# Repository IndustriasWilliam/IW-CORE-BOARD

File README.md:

"# IW-CORE-BOARD" 
cmd.exe /C copy/Y "${BuildArtifactFileBaseName}.elf" "..\QSPI_FlashLoader.stldr"

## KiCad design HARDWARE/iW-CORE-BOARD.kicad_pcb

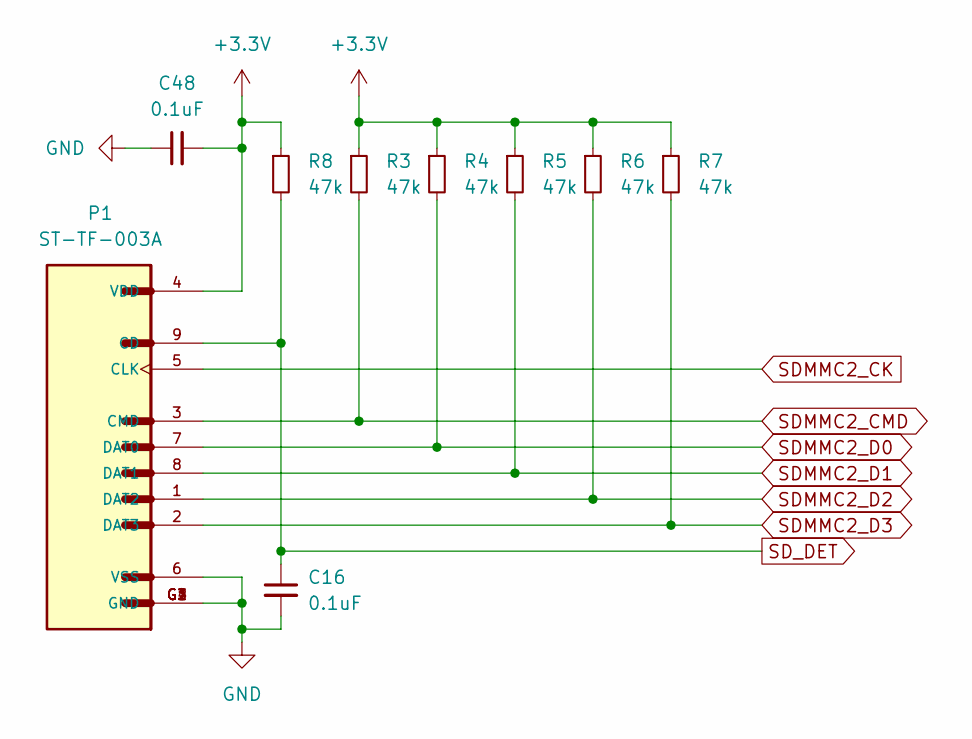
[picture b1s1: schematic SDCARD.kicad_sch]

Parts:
C16, C48: 0.1uF; C_0603_1608Metric
P1: ST-TF-003A; SUNTECH_ST-TF-003A
R3, R4, R5, R6, R7, R8: 47k; R_0603_1608Metric

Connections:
+3.3V: C48.2, P1.4 (VDD), R3.1, R4.1, R5.1, R6.1, R7.1, R8.1; also elsewhere on the board
GND: C16.2, C48.1, P1.6 (VSS), P1.G1 (GND), P1.G2 (GND), P1.G3 (GND), P1.G4 (GND); also elsewhere on the board
SDMMC2_CK: P1.5 (CLK); also elsewhere on the board
SDMMC2_CMD: P1.3 (CMD), R3.2; also elsewhere on the board
SDMMC2_D0: P1.7 (DAT0), R4.2; also elsewhere on the board
SDMMC2_D1: P1.8 (DAT1), R5.2; also elsewhere on the board
SDMMC2_D2: P1.1 (DAT2), R6.2; also elsewhere on the board
SDMMC2_D3: P1.2 (DAT3), R7.2; also elsewhere on the board
SD_DET: C16.1, P1.9 (CD), R8.2; also elsewhere on the board

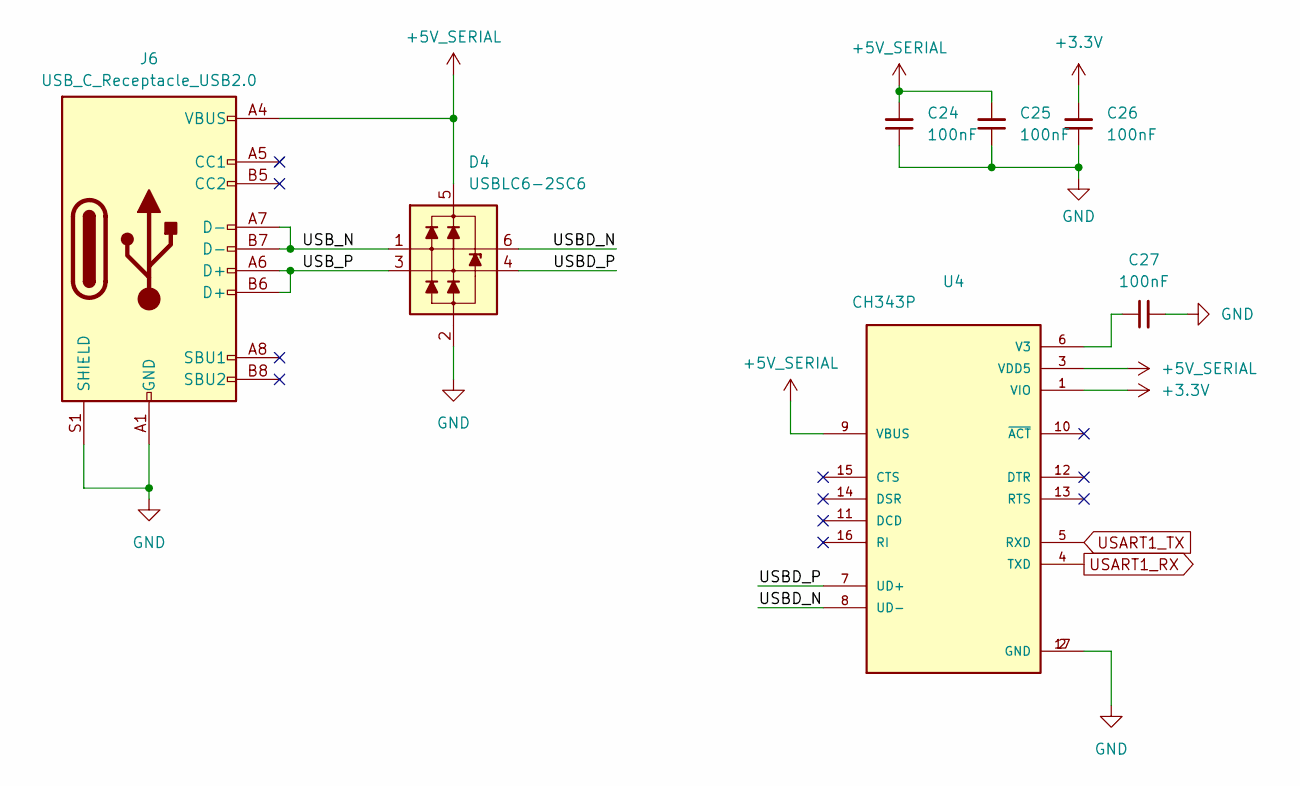
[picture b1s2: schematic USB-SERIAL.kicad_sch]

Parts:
C24, C25, C26, C27: 100nF; C_0603_1608Metric
D4: USBLC6-2SC6; SOT-23-6
J6: USB_C_Receptacle_USB2.0; USB_C_Receptacle_G-Switch_GT-USB-7010ASV
U4: CH343P; QFN50P300X300X80-17N; PARTREV 1E

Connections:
+3.3V: C26.2, U4.1 (VIO); also elsewhere on the board
+5V_SERIAL: C24.2, C25.2, D4.5 (VP), J6.A4 (VBUS), J6.A9 (VBUS), J6.B4 (VBUS), J6.B9 (VBUS), U4.3 (VDD5), U4.9 (VBUS); also elsewhere on the board
/USB-SERIAL/USBD_N: D4.6 (L1), U4.8 (UD-)
/USB-SERIAL/USBD_P: D4.4 (L2), U4.7 (UD+)
/USB-SERIAL/USB_N: D4.1 (L1), J6.A7 (D-), J6.B7 (D-)
/USB-SERIAL/USB_P: D4.3 (L2), J6.A6 (D+), J6.B6 (D+)
GND: C24.1, C25.1, C26.1, C27.2, D4.2 (VN), J6.A1 (GND), J6.A12 (GND), J6.B1 (GND), J6.B12 (GND), J6.S1 (SHIELD), U4.2 (GND), U4.17 (GND); also elsewhere on the board
unnamed: C27.1, U4.6 (V3)
USART1_RX: U4.4 (TXD); also elsewhere on the board
USART1_TX: U4.5 (RXD); also elsewhere on the board

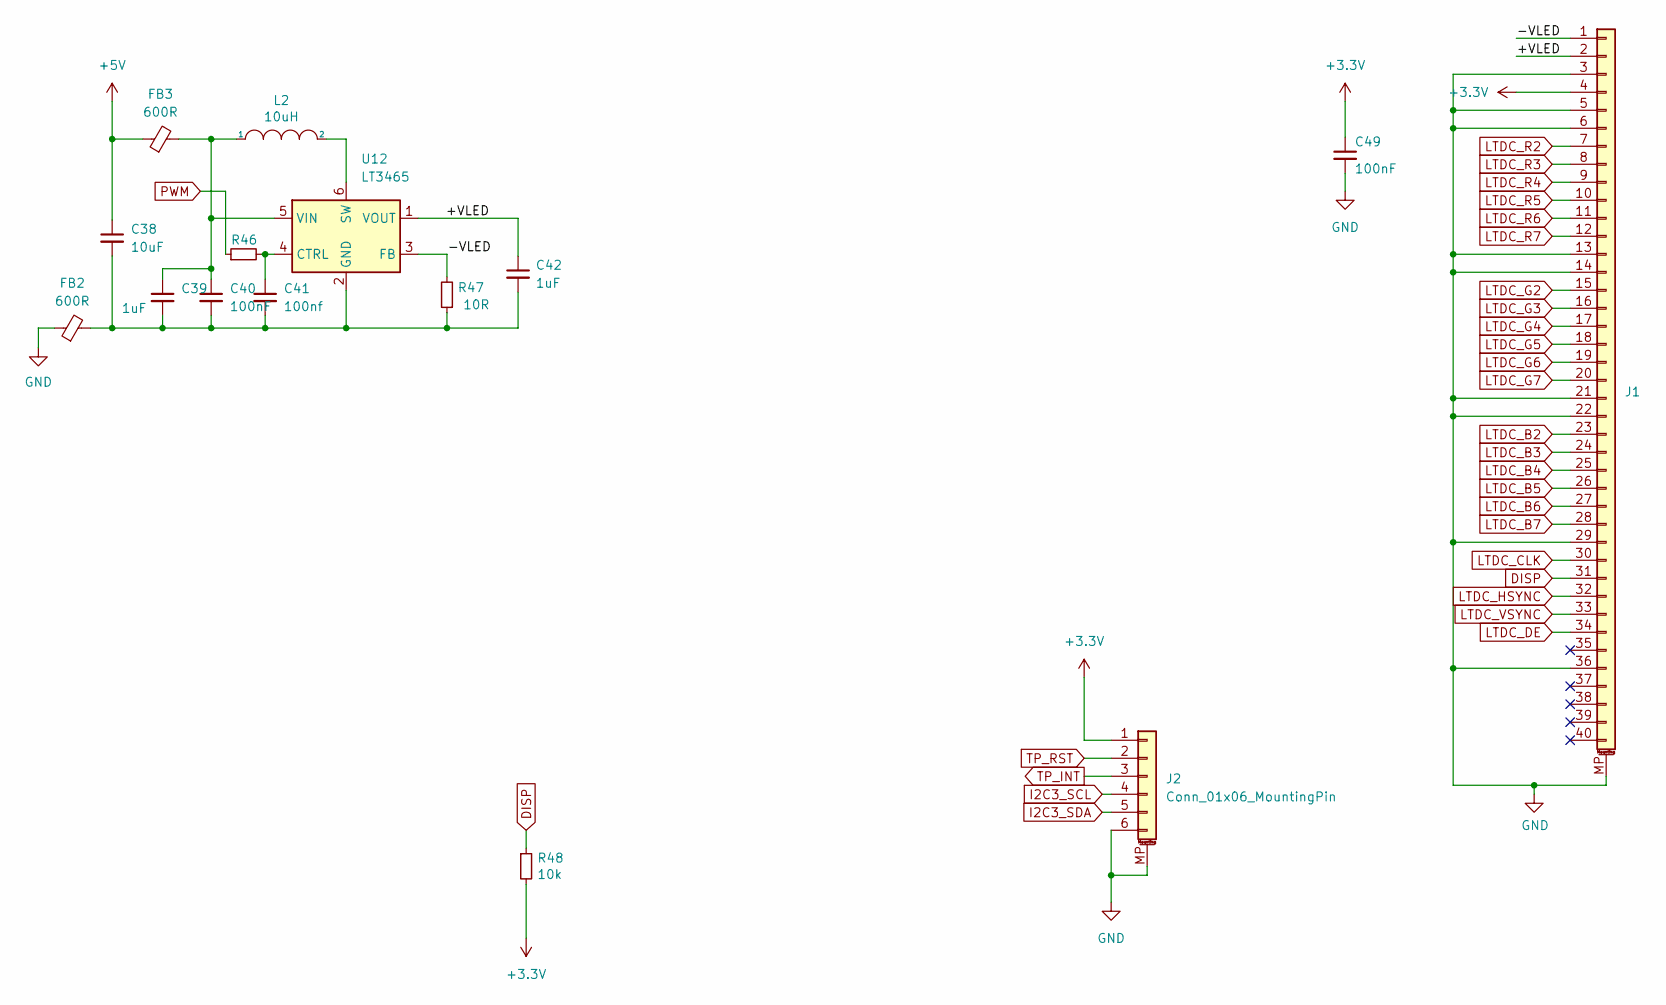
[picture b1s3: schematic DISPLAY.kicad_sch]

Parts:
C38: 10uF; C_0805_2012Metric
C39, C42: 1uF; C_0603_1608Metric
C40, C49: 100nF; C_0603_1608Metric
C41: 100nf; C_0603_1608Metric
FB2, FB3: 600R; L_0603_1608Metric
J1: Conn_01x40_MountingPin; TE_4-1734839-0_1x40-1MP_P0.5mm_Horizontal
J2: Conn_01x06_MountingPin; TE_0-1734839-6_1x06-1MP_P0.5mm_Horizontal
L2: 10uH; L_0805_2012Metric
R46: 5k; R_0603_1608Metric
R47: 10R; R_0603_1608Metric
R48: 10k; R_0603_1608Metric
U12: LT3465; TSOT-23-6

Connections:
+3.3V: C49.1, J1.4, J2.1, R48.2; also elsewhere on the board
+5V: C38.1, FB3.1; also elsewhere on the board
/DISPLAY/+VLED: C42.1, J1.2, U12.1 (VOUT)
/DISPLAY/-VLED: J1.1, R47.2, U12.3 (FB)
DISP: J1.31, R48.1
GND: C49.2, FB2.1, J1.3, J1.5, J1.6, J1.13, J1.14, J1.21, J1.22, J1.29, J1.36, J1.MP (MountPin), J2.6, J2.MP (MountPin); also elsewhere on the board
I2C3_SCL: J2.4; also elsewhere on the board
I2C3_SDA: J2.5; also elsewhere on the board
LTDC_B2: J1.23; also elsewhere on the board
LTDC_B3: J1.24; also elsewhere on the board
LTDC_B4: J1.25; also elsewhere on the board
LTDC_B5: J1.26; also elsewhere on the board
LTDC_B6: J1.27; also elsewhere on the board
LTDC_B7: J1.28; also elsewhere on the board
LTDC_CLK: J1.30; also elsewhere on the board
LTDC_DE: J1.34; also elsewhere on the board
LTDC_G2: J1.15; also elsewhere on the board
LTDC_G3: J1.16; also elsewhere on the board
LTDC_G4: J1.17; also elsewhere on the board
LTDC_G5: J1.18; also elsewhere on the board
LTDC_G6: J1.19; also elsewhere on the board
LTDC_G7: J1.20; also elsewhere on the board
LTDC_HSYNC: J1.32; also elsewhere on the board
LTDC_R2: J1.7; also elsewhere on the board
LTDC_R3: J1.8; also elsewhere on the board
LTDC_R4: J1.9; also elsewhere on the board
LTDC_R5: J1.10; also elsewhere on the board
LTDC_R6: J1.11; also elsewhere on the board
LTDC_R7: J1.12; also elsewhere on the board
LTDC_VSYNC: J1.33; also elsewhere on the board
unnamed: C41.1, R46.2, U12.4 (CTRL)
unnamed: C38.2, C39.2, C40.2, C41.2, C42.2, FB2.2, R47.1, U12.2 (GND)
unnamed: L2.2, U12.6 (SW)
unnamed: C39.1, C40.1, FB3.2, L2.1, U12.5 (VIN)
PWM: R46.1; also elsewhere on the board
TP_INT: J2.3; also elsewhere on the board
TP_RST: J2.2; also elsewhere on the board

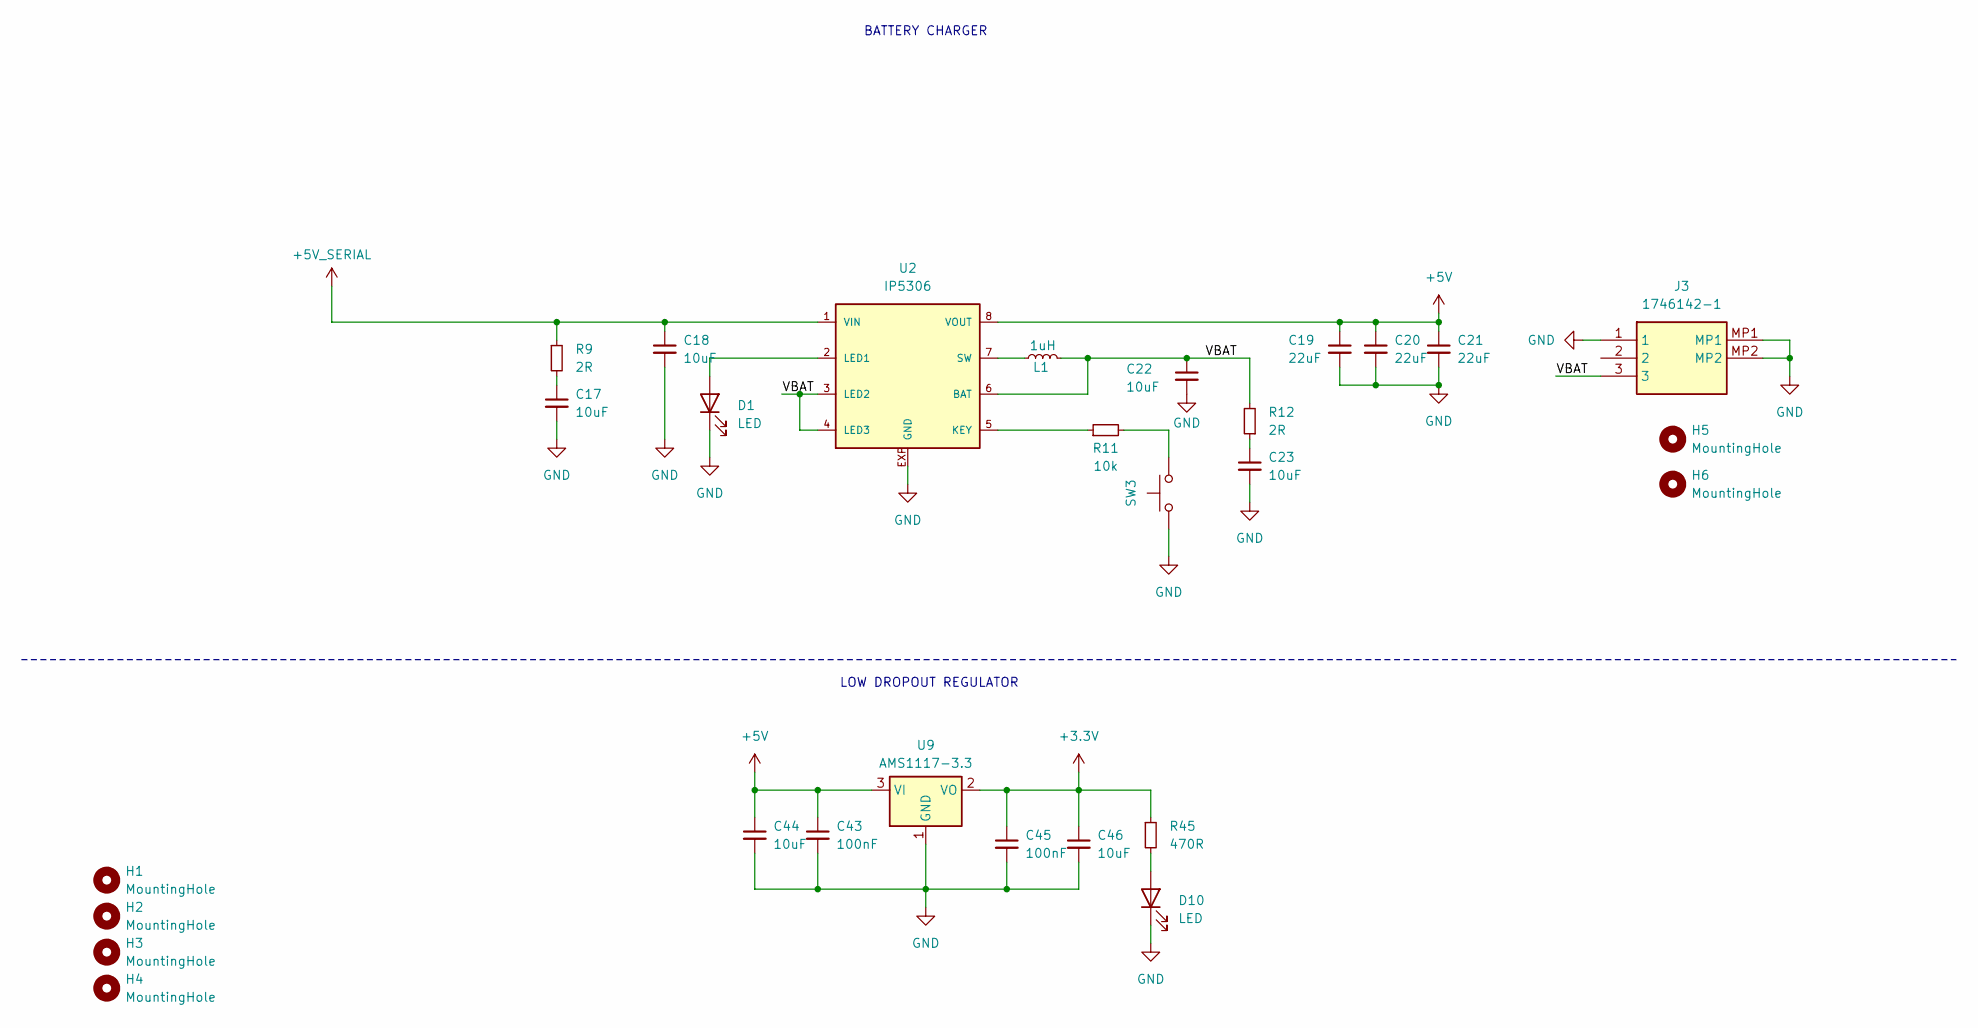
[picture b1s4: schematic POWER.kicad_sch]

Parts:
C17, C18, C44, C46: 10uF; C_0805_2012Metric
C19, C20, C21: 22uF; C_1206_3216Metric
C22, C23: 10uF; C_0603_1608Metric
C43, C45: 100nF; C_0603_1608Metric
D1, D10: LED; LED_0603_1608Metric
H1, H2, H3, H4: MountingHole; MountingHole_2.5mm_Pad
H5, H6: MountingHole; MountingHole_2.5mm
J3: 1746142-1; 17461421; Manufacturer_Part_Number 1746142-1; Mouser Part Number 571-1746142-1
L1: 1uH; L_APV_ANR6020
R9, R12: 2R; R_0603_1608Metric
R11: 10k; R_0603_1608Metric
R45: 470R; R_0603_1608Metric
SW3: SW_Push; SW_Push_1P1T-MP_NO_Horizontal_Alps_SKRTLAE010
U2: IP5306; SOP8-P
U9: AMS1117-3.3; SOT-223-3_TabPin2

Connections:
+3.3V: C45.1, C46.1, R45.1, U9.2 (VO); also elsewhere on the board
+5V: C19.1, C20.1, C21.1, C43.1, C44.1, U2.8 (VOUT), U9.3 (VI); also elsewhere on the board
+5V_SERIAL: C18.1, R9.1, U2.1 (VIN); also elsewhere on the board
/POWER/VBAT: C22.1, J3.3, L1.2, R12.2, U2.3 (LED2), U2.4 (LED3), U2.6 (BAT)
GND: C17.2, C18.2, C19.2, C20.2, C21.2, C22.2, C23.2, C43.2, C44.2, C45.2, C46.2, D1.1 (K), D10.1 (K), J3.1, J3.MP1, J3.MP2, SW3.1, U2.EXP (GND), U9.1 (GND); also elsewhere on the board
unnamed: C17.1, R9.2
unnamed: C23.1, R12.1
unnamed: D1.2 (A), U2.2 (LED1)
unnamed: D10.2 (A), R45.2
unnamed: R11.2, SW3.2
unnamed: R11.1, U2.5 (KEY)
unnamed: L1.1, U2.7 (SW)

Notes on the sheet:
BATTERY CHARGER
LOW DROPOUT REGULATOR

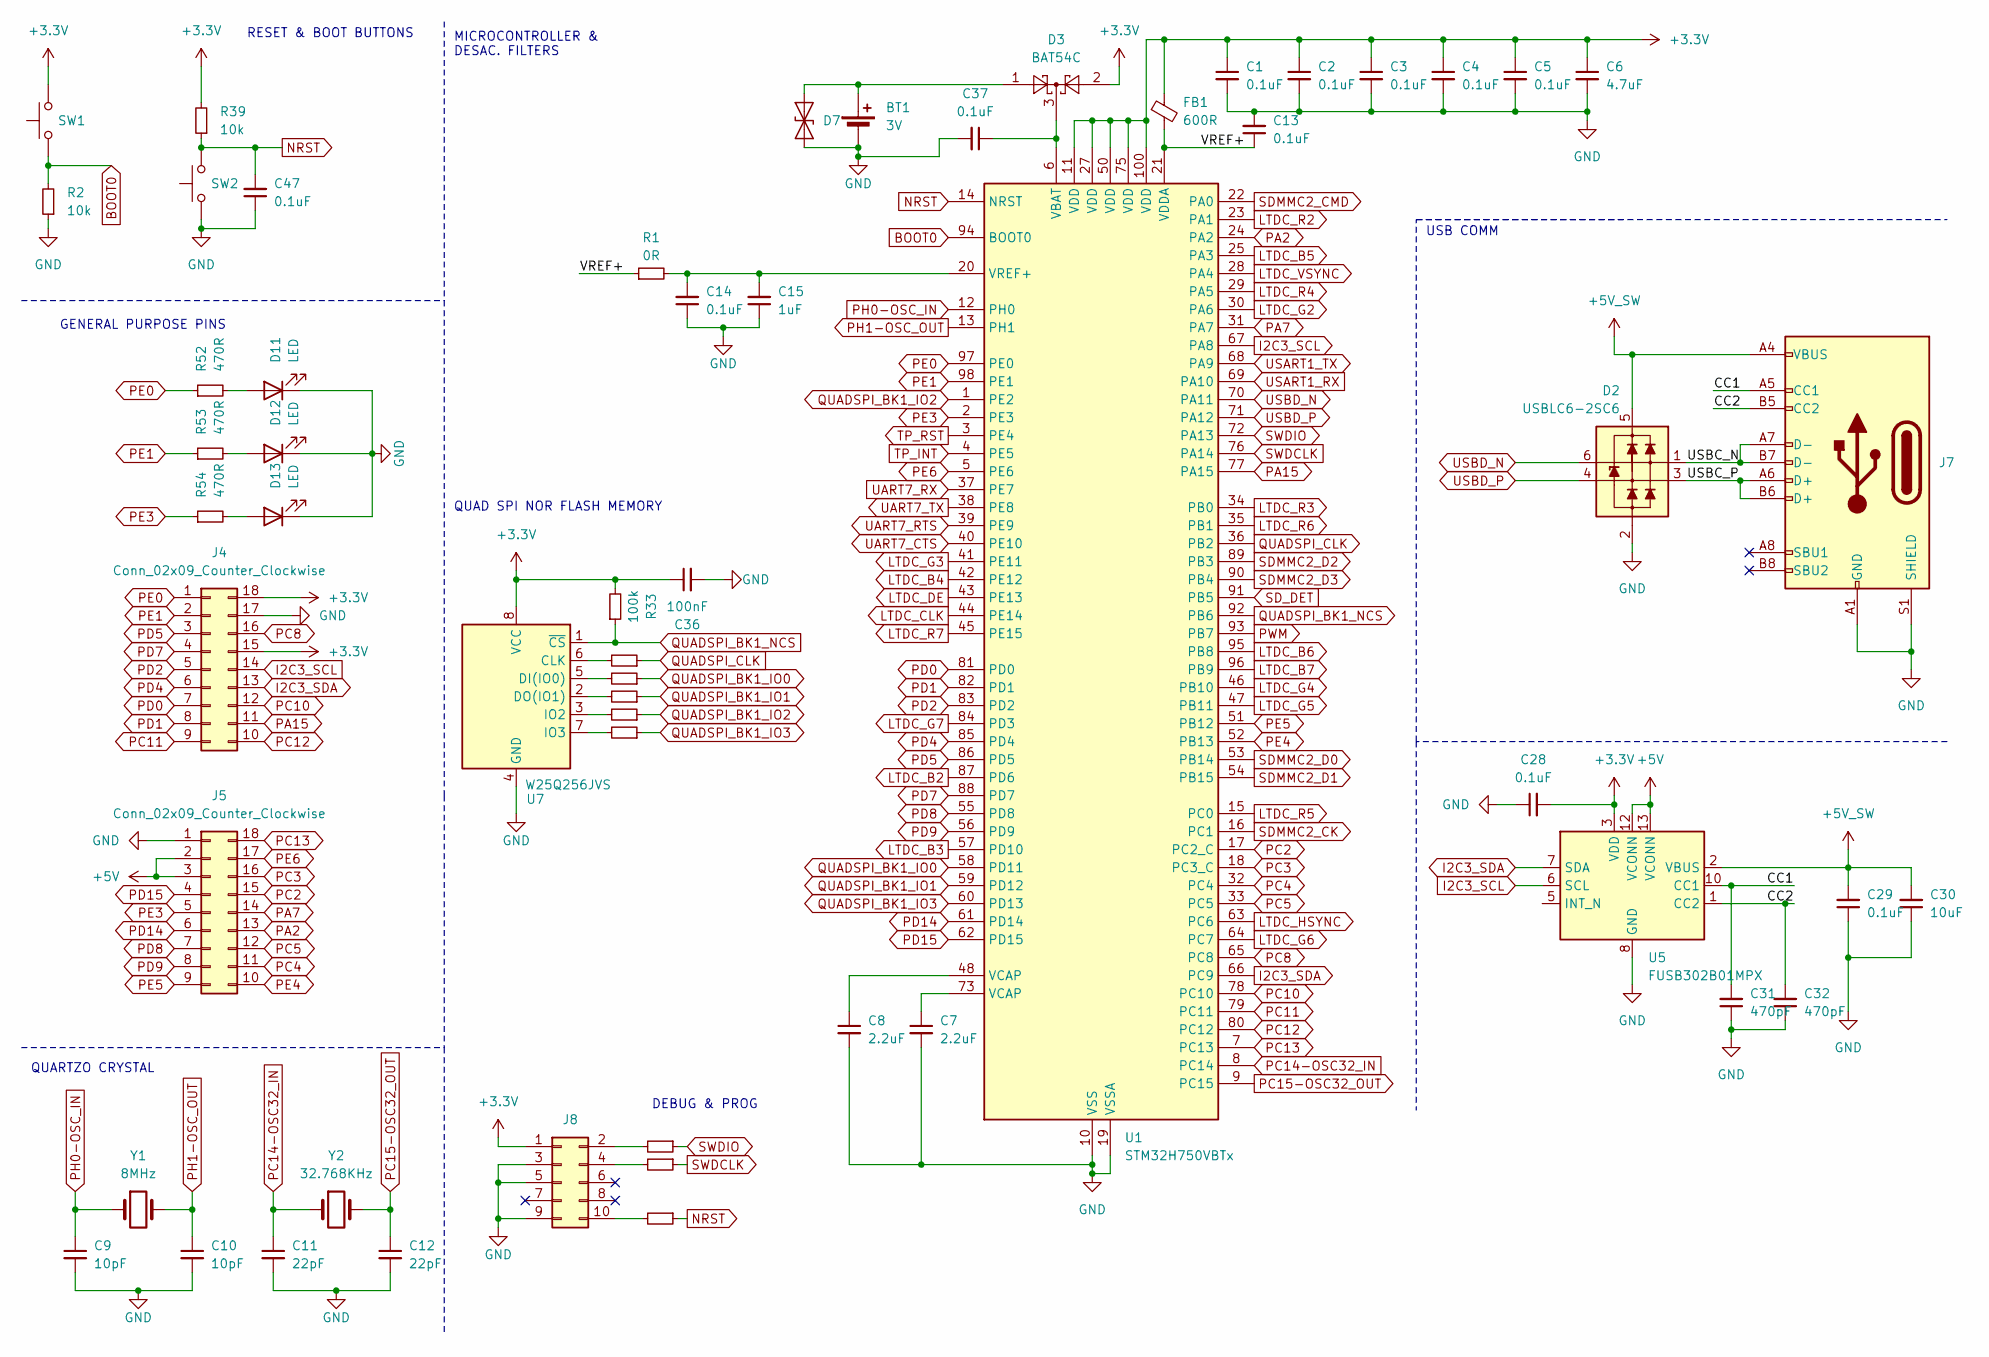
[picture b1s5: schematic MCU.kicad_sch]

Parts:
BT1: 3V; BS-12-B-1A
C1, C2, C3, C4, C5, C13, C14, C28, C29, C37, C47: 0.1uF; C_0603_1608Metric
C6: 4.7uF; C_0603_1608Metric
C7, C8: 2.2uF; C_0603_1608Metric
C9, C10: 10pF; C_0603_1608Metric
C11, C12: 22pF; C_0603_1608Metric
C15: 1uF; C_0603_1608Metric
C30: 10uF; C_1206_3216Metric
C31, C32: 470pF; C_0603_1608Metric
C36: 100nF; C_0603_1608Metric
D2: USBLC6-2SC6; SOT-23-6
D3: BAT54C; SOT-23
D7: ESD9B3.3ST5G; D_SOD-923
D11, D12, D13: LED; LED_0603_1608Metric
FB1: 600R; L_0603_1608Metric
J4, J5: Conn_02x09_Counter_Clockwise; PinSocket_2x09_P2.54mm_Vertical_SMD
J7: USB_C_Receptacle_USB2.0; USB_C_Receptacle_G-Switch_GT-USB-7010ASV
J8: Conn_02x05_Odd_Even; PinHeader_2x05_P1.27mm_Vertical_SMD
R1: 0R; R_0603_1608Metric
R2, R39: 10k; R_0603_1608Metric
R28, R29, R30, R31, R32: 33R; R_0603_1608Metric
R33: 100k; R_0603_1608Metric
R41, R42, R44: 22R; R_0603_1608Metric
R52, R53, R54: 470R; R_0603_1608Metric
SW1, SW2: SW_Push; SW_SPST_CK_RS282G05A3
U1: STM32H750VBTx; LQFP-100_14x14mm_P0.5mm
U5: FUSB302B01MPX; WQFN-14-1EP_2.5x2.5mm_P0.5mm_EP1.45x1.45mm
U7: W25Q256JVS; WSON-8-1EP_8x6mm_P1.27mm_EP3.4x4.3mm
Y1: 8MHz; Crystal_SMD_Abracon_ABM3-2Pin_5.0x3.2mm
Y2: 32.768KHz; Crystal_SMD_3215-2Pin_3.2x1.5mm

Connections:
+3.3V: C1.1, C2.1, C3.1, C4.1, C5.1, C6.1, C28.2, C36.1, D3.2, FB1.1, J4.15, J4.18, J8.1, R33.2, R39.2, SW1.2, U1.11 (VDD), U1.27 (VDD), U1.50 (VDD), U1.75 (VDD), U1.100 (VDD), U5.3 (VDD), U5.4 (VDD), U7.8 (VCC); also elsewhere on the board
+5V: J5.2, J5.3, U5.12 (VCONN), U5.13 (VCONN); also elsewhere on the board
+5V_SW: C29.2, C30.2, D2.5 (VP), J7.A4 (VBUS), J7.A9 (VBUS), J7.B4 (VBUS), J7.B9 (VBUS), U5.2 (VBUS)
/MCU/CC1: C31.2, J7.A5 (CC1), U5.10 (CC1), U5.11 (CC1)
/MCU/CC2: C32.2, J7.B5 (CC2), U5.1 (CC2), U5.14 (CC2)
/MCU/USBC_N: D2.1 (L1), J7.A7 (D-), J7.B7 (D-)
/MCU/USBC_P: D2.3 (L2), J7.A6 (D+), J7.B6 (D+)
/MCU/VREF+: C13.1, FB1.2, R1.1, U1.21 (VDDA)
BOOT0: R2.2, SW1.1, U1.94 (BOOT0)
GND: BT1.2 (-), C1.2, C2.2, C3.2, C4.2, C5.2, C6.2, C7.2, C8.2, C9.2, C10.2, C11.2, C12.2, C13.2, C14.1, C15.1, C28.1, C29.1, C30.1, C31.1, C32.1, C36.2, C37.2, C47.1, D2.2 (VN), D7.1 (A1), D11.1 (K), D12.1 (K), D13.1 (K), J4.17, J5.1, J7.A1 (GND), J7.A12 (GND), J7.B1 (GND), J7.B12 (GND), J7.S1 (SHIELD), J8.3, J8.5, J8.9, R2.1, SW2.1, U1.10 (VSS), U1.19 (VSSA), U1.26 (VSS), U1.49 (VSS), U1.74 (VSS), U1.99 (VSS), U5.8 (GND), U5.9 (GND), U5.15 (GND), U7.4 (GND); also elsewhere on the board
I2C3_SCL: J4.14, U1.67 (PA8), U5.6 (SCL); also elsewhere on the board
I2C3_SDA: J4.13, U1.66 (PC9), U5.7 (SDA); also elsewhere on the board
LTDC_B2: U1.87 (PD6); also elsewhere on the board
LTDC_B3: U1.57 (PD10); also elsewhere on the board
LTDC_B4: U1.42 (PE12); also elsewhere on the board
LTDC_B5: U1.25 (PA3); also elsewhere on the board
LTDC_B6: U1.95 (PB8); also elsewhere on the board
LTDC_B7: U1.96 (PB9); also elsewhere on the board
LTDC_CLK: U1.44 (PE14); also elsewhere on the board
LTDC_DE: U1.43 (PE13); also elsewhere on the board
LTDC_G2: U1.30 (PA6); also elsewhere on the board
LTDC_G3: U1.41 (PE11); also elsewhere on the board
LTDC_G4: U1.46 (PB10); also elsewhere on the board
LTDC_G5: U1.47 (PB11); also elsewhere on the board
LTDC_G6: U1.64 (PC7); also elsewhere on the board
LTDC_G7: U1.84 (PD3); also elsewhere on the board
LTDC_HSYNC: U1.63 (PC6); also elsewhere on the board
LTDC_R2: U1.23 (PA1); also elsewhere on the board
LTDC_R3: U1.34 (PB0); also elsewhere on the board
LTDC_R4: U1.29 (PA5); also elsewhere on the board
LTDC_R5: U1.15 (PC0); also elsewhere on the board
LTDC_R6: U1.35 (PB1); also elsewhere on the board
LTDC_R7: U1.45 (PE15); also elsewhere on the board
LTDC_VSYNC: U1.28 (PA4); also elsewhere on the board
NRST: C47.2, R39.1, R44.1, SW2.2, U1.14 (NRST)
unnamed: BT1.1 (+), D3.1, D7.2 (A2)
unnamed: C7.1, U1.73 (VCAP)
unnamed: C8.1, U1.48 (VCAP)
unnamed: D11.2 (A), R52.2
unnamed: D12.2 (A), R53.2
unnamed: D13.2 (A), R54.2
unnamed: J8.2, R41.2
unnamed: J8.4, R42.2
unnamed: J8.10, R44.2
unnamed: C37.1, D3.3, U1.6 (VBAT)
unnamed: C14.2, C15.2, R1.2, U1.20 (VREF+)
unnamed: R32.2, U7.6 (CLK)
unnamed: R28.2, U7.5 (DI(IO0))
unnamed: R29.2, U7.2 (DO(IO1))
unnamed: R30.2, U7.3 (IO2)
unnamed: R31.2, U7.7 (IO3)
PA2: J5.13, U1.24 (PA2)
PA7: J5.14, U1.31 (PA7)
PA15: J4.11, U1.77 (PA15)
PC2: J5.15, U1.17 (PC2_C)
PC3: J5.16, U1.18 (PC3_C)
PC4: J5.11, U1.32 (PC4)
PC5: J5.12, U1.33 (PC5)
PC8: J4.16, U1.65 (PC8)
PC10: J4.12, U1.78 (PC10)
PC11: J4.9, U1.79 (PC11)
PC12: J4.10, U1.80 (PC12)
PC13: J5.18, U1.7 (PC13)
PC14-OSC32_IN: C11.1, U1.8 (PC14), Y2.1
PC15-OSC32_OUT: C12.1, U1.9 (PC15), Y2.2
PD0: J4.7, U1.81 (PD0)
PD1: J4.8, U1.82 (PD1)
PD2: J4.5, U1.83 (PD2)
PD4: J4.6, U1.85 (PD4)
PD5: J4.3, U1.86 (PD5)
PD7: J4.4, U1.88 (PD7)
PD8: J5.7, U1.55 (PD8)
PD9: J5.8, U1.56 (PD9)
PD14: J5.6, U1.61 (PD14)
PD15: J5.4, U1.62 (PD15)
PE0: J4.1, R52.1, U1.97 (PE0)
PE1: J4.2, R53.1, U1.98 (PE1)
PE3: J5.5, R54.1, U1.2 (PE3)
PE4: J5.10, U1.52 (PB13)
PE5: J5.9, U1.51 (PB12)
PE6: J5.17, U1.5 (PE6)
PH0-OSC_IN: C9.1, U1.12 (PH0), Y1.1
PH1-OSC_OUT: C10.1, U1.13 (PH1), Y1.2
PWM: U1.93 (PB7); also elsewhere on the board
QUADSPI_BK1_IO0: R28.1, U1.58 (PD11)
QUADSPI_BK1_IO1: R29.1, U1.59 (PD12)
QUADSPI_BK1_IO2: R30.1, U1.1 (PE2)
QUADSPI_BK1_IO3: R31.1, U1.60 (PD13)
QUADSPI_BK1_NCS: R33.1, U1.92 (PB6), U7.1 (~CS)
QUADSPI_CLK: R32.1, U1.36 (PB2)
SDMMC2_CK: U1.16 (PC1); also elsewhere on the board
SDMMC2_CMD: U1.22 (PA0); also elsewhere on the board
SDMMC2_D0: U1.53 (PB14); also elsewhere on the board
SDMMC2_D1: U1.54 (PB15); also elsewhere on the board
SDMMC2_D2: U1.89 (PB3); also elsewhere on the board
SDMMC2_D3: U1.90 (PB4); also elsewhere on the board
SD_DET: U1.91 (PB5); also elsewhere on the board
SWDCLK: R42.1, U1.76 (PA14)
SWDIO: R41.1, U1.72 (PA13)
TP_INT: U1.4 (PE5); also elsewhere on the board
TP_RST: U1.3 (PE4); also elsewhere on the board
UART7_CTS: U1.40 (PE10)
UART7_RTS: U1.39 (PE9)
UART7_RX: U1.37 (PE7)
UART7_TX: U1.38 (PE8)
USART1_RX: U1.69 (PA10); also elsewhere on the board
USART1_TX: U1.68 (PA9); also elsewhere on the board
USBD_N: D2.6 (L1), U1.70 (PA11)
USBD_P: D2.4 (L2), U1.71 (PA12)

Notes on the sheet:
GENERAL PURPOSE PINS
QUARTZO CRYSTAL
USB COMM
MICROCONTROLLER & DESAC. FILTERS
RESET & BOOT BUTTONS
QUAD SPI NOR FLASH MEMORY
DEBUG & PROG

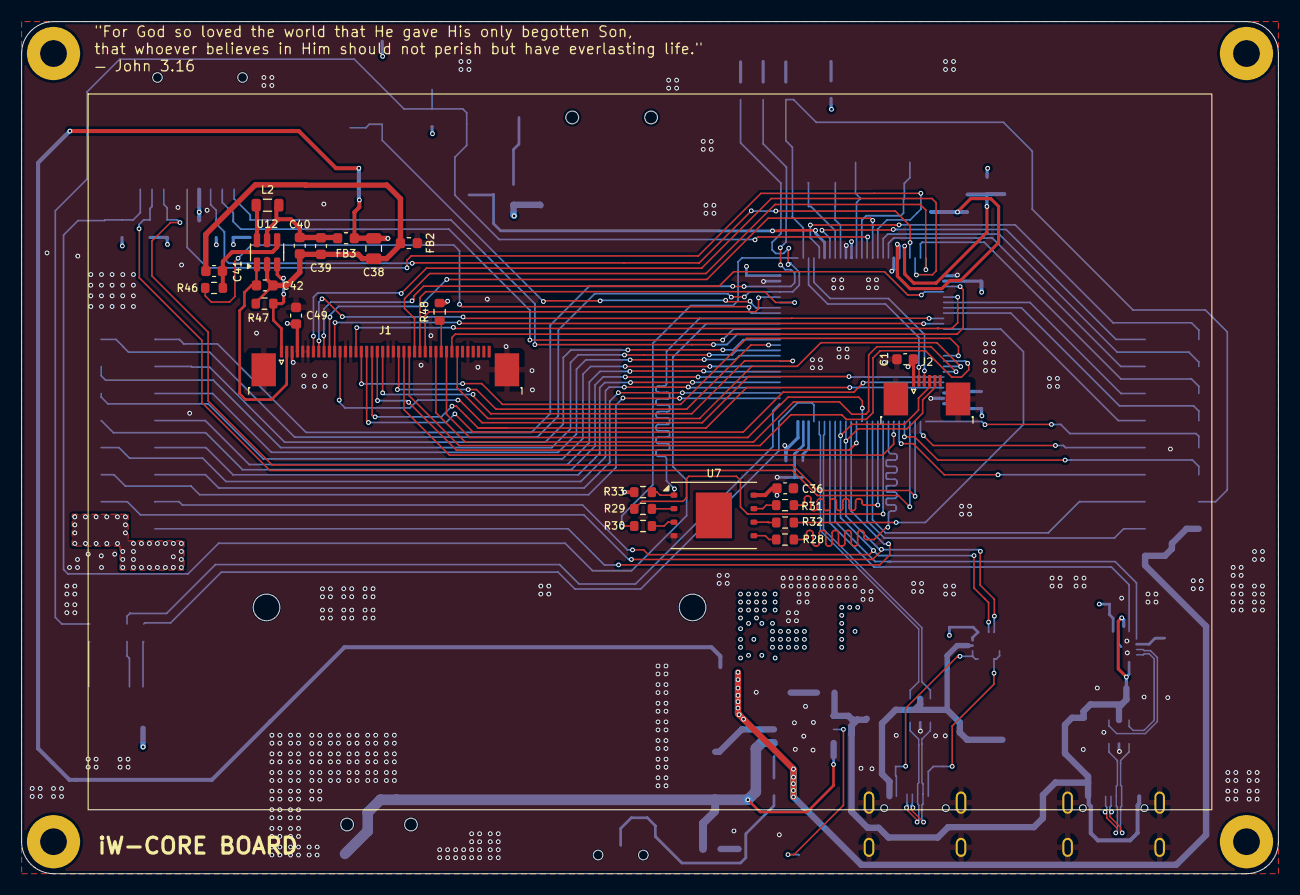
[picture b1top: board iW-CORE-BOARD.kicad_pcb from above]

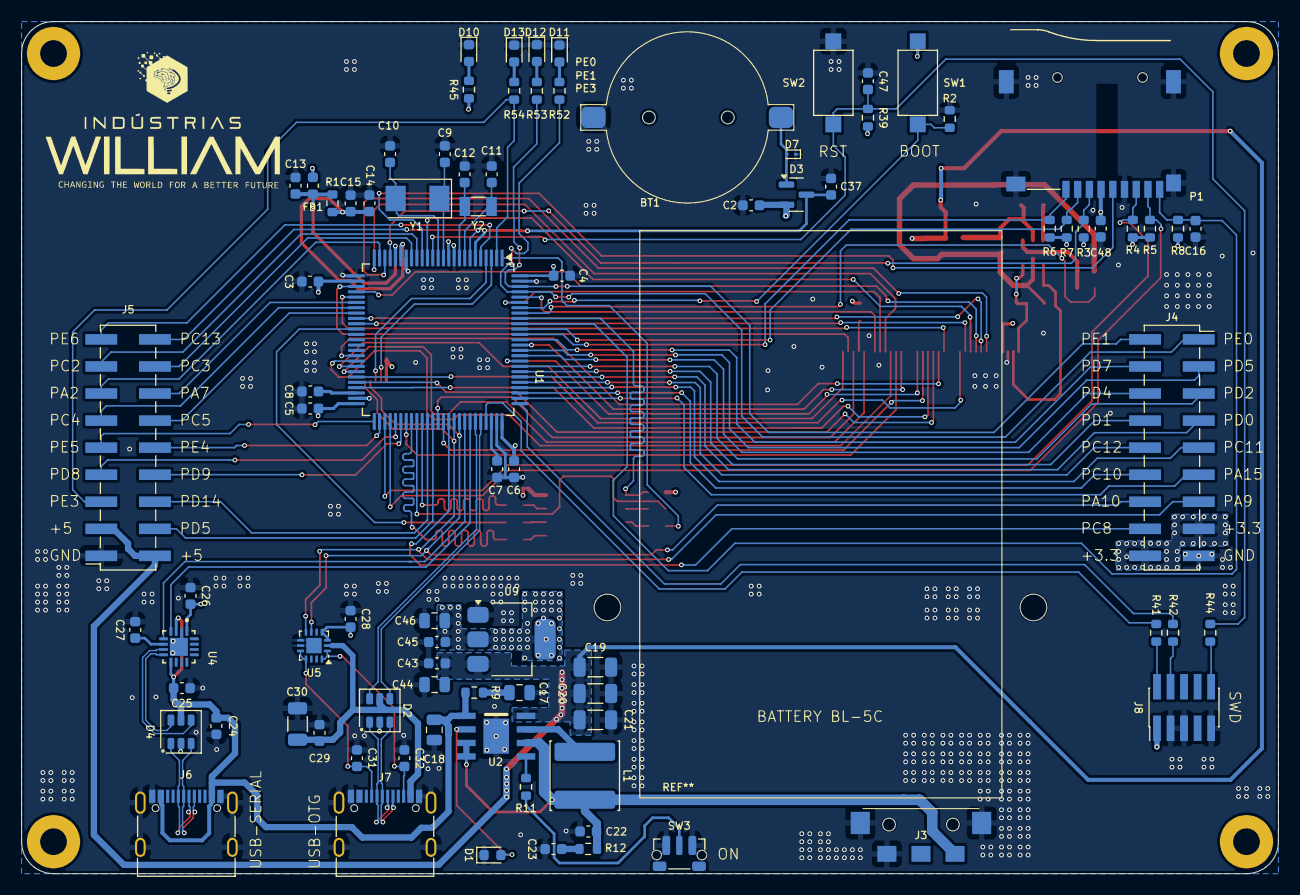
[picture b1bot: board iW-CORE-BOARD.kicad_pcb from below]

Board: 4 copper layers, 118.0 x 80.0 mm, 116 parts (86 on the bottom side), 126 nets.

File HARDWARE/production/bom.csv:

Designator,Footprint,Quantity,Value,LCSC Part #
BT1,BS-12-B-1A,1,3V,
"C1, C13, C14, C16, C2, C3, C32, C33, C34, C35, C37, C4, C47, C48, C5, C51, C52",0603,17,0.1uF,
"C10, C9",0603,2,10pF,
"C11, C12",0603,2,22pF,
"C15, C39, C42",0603,3,1uF,
"C17, C18, C38, C44, C46",0805,5,10uF,
"C19, C20, C21",1206,3,22uF,
"C22, C23",0603,2,10uF,
"C36, C40, C41, C43, C45, C49",0603,6,100nF,
C6,0603,1,4.7uF,
"C7, C8",0603,2,2.2uF,
"D1, D10, D11, D12, D13, D4",0603,6,LED,
"D2, D5",D_SOD-323,2,1N5819WS,
D3,SOT-23,1,BAT54C,
D7,D_SOD-923,1,ESD9B3.3ST5G,
"FB1, FB2, FB3",0603,3,600R,
"H1, H2, H3, H4",MountingHole_2.5mm_Pad,4,MountingHole,
J1,TE_4-1734839-0_1x40-1MP_P0.5mm_Horizontal,1,Conn_01x40_MountingPin,
J2,TE_0-1734839-6_1x06-1MP_P0.5mm_Horizontal,1,Conn_01x06_MountingPin,
J3,17461421,1,1746142-1,
"J4, J5",PinSocket_2x09_P2.54mm_Vertical_SMD,2,Conn_02x09_Counter_Clockwise,
"J7, J9",USB_C_Receptacle_G-Switch_GT-USB-7010ASV,2,USB_C_Receptacle_USB2.0,
J8,PinHeader_2x05_P1.27mm_Vertical_SMD,1,Conn_02x05_Odd_Even,
L1,L_APV_ANR6020,1,1uH,
L2,0805,1,10uH,
P1,SUNTECH_ST-TF-003A,1,ST-TF-003A,
R1,0603,1,0R,
"R11, R2, R39, R48",0603,4,10k,
"R12, R9",0603,2,2R,
"R28, R29, R30, R31, R32",0603,5,33R,
"R3, R4, R5, R6, R7, R8",0603,6,47k,
R33,0603,1,100k,
"R41, R42, R44",0603,3,22R,
"R45, R52, R53, R54",0603,4,470R,
R46,0603,1,5k,
R47,0603,1,10R,
"R50, R51",0603,2,220R,
"SW1, SW2",SW_SPST_CK_RS282G05A3,2,SW_Push,
SW3,SW_Push_1P1T-MP_NO_Horizontal_Alps_SKRTLAE010,1,SW_Push,
U1,LQFP-100_14x14mm_P0.5mm,1,STM32H750VBTx,
"U10, U11",SOT-23-6,2,USBLC6-2SC6,
U12,TSOT-23-6,1,LT3465,
U2,SOP8-P,1,IP5306,
U3,LQFP-48_7x7mm_P0.5mm,1,STM32F072CBT6,
U7,WSON-8-1EP_8x6mm_P1.27mm_EP3.4x4.3mm,1,W25Q256JVS,
U9,SOT-223-3_TabPin2,1,AMS1117-3.3,
Y1,Crystal_SMD_Abracon_ABM3-2Pin_5.0x3.2mm,1,8MHz,
Y2,Crystal_SMD_3215-2Pin_3.2x1.5mm,1,32.768KHz,

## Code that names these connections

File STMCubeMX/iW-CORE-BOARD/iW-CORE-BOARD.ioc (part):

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Mcu.Name=STM32H750VBTx
Mcu.Package=LQFP100
Mcu.UserName=STM32H750VBTx
PA0.Mode=SD_4_bits_Wide_bus
PA0.Signal=SDMMC2_CMD
PA10.Mode=Asynchronous
PA10.Signal=USART1_RX
PA11.Mode=Host_Only
PA11.Signal=USB_OTG_FS_DM
PA12.Mode=Host_Only
PA12.Signal=USB_OTG_FS_DP
PA15\ (JTDI).Signal=SPI3_NSS
PA3.Mode=RGB565
PA3.Signal=LTDC_B5
PA4.Mode=RGB565
PA4.Signal=LTDC_VSYNC
PA5.Mode=RGB565
PA5.Signal=LTDC_R4
PA6.Mode=RGB565
PA6.Signal=LTDC_G2
PA8.GPIOParameters=GPIO_Speed,GPIO_Pu
PA8.GPIO_Pu=GPIO_PULLUP
PA8.GPIO_Speed=GPIO_SPEED_FREQ_MEDIUM
PA8.Mode=I2C
PA8.Signal=I2C3_SCL
PA9.Mode=Asynchronous
PA9.Signal=USART1_TX
PB0.Mode=RGB565
PB0.Signal=LTDC_R3
PB1.Mode=RGB565
PB1.Signal=LTDC_R6
PB10.Mode=RGB565
PB10.Signal=LTDC_G4
PB11.Mode=RGB565
PB11.Signal=LTDC_G5
PB14.Mode=SD_4_bits_Wide_bus
PB14.Signal=SDMMC2_D0
PB15.Mode=SD_4_bits_Wide_bus
PB15.Signal=SDMMC2_D1
PB2.Mode=Single Bank 1
PB2.Signal=QUADSPI_CLK
PB3\ (JTDO/TRACESWO).Mode=SD_4_bits_Wide_bus
PB3\ (JTDO/TRACESWO).Signal=SDMMC2_D2
PB4\ (NJTRST).Mode=SD_4_bits_Wide_bus
PB4\ (NJTRST).Signal=SDMMC2_D3
PB6.Mode=Single Bank 1
PB6.Signal=QUADSPI_BK1_NCS
PB7.GPIOParameters=GPIO_Label
PB7.GPIO_Label=PWM_BACKLIGHT
PB7.Signal=S_TIM4_CH2
PB8.Mode=RGB565
PB8.Signal=LTDC_B6
PB9.Mode=RGB565
PB9.Signal=LTDC_B7
PC0.Mode=RGB565
PC0.Signal=LTDC_R5
PC1.Mode=SD_4_bits_Wide_bus
PC1.Signal=SDMMC2_CK
PC10.Signal=SPI3_SCK
PC11.Signal=SPI3_MISO
PC12.Signal=SPI3_MOSI
PC14-OSC32_IN\ (OSC32_IN).Mode=LSE-External-Oscillator
PC14-OSC32_IN\ (OSC32_IN).Signal=RCC_OSC32_IN
PC15-OSC32_OUT\ (OSC32_OUT).Mode=LSE-External-Oscillator
PC15-OSC32_OUT\ (OSC32_OUT).Signal=RCC_OSC32_OUT
PC6.Mode=RGB565
PC6.Signal=LTDC_HSYNC
PC7.Mode=RGB565
PC7.Signal=LTDC_G6
PC9.GPIOParameters=GPIO_Speed,GPIO_Pu
PC9.GPIO_Pu=GPIO_PULLUP
PC9.GPIO_Speed=GPIO_SPEED_FREQ_MEDIUM
PC9.Mode=I2C
PC9.Signal=I2C3_SDA
PD0.Signal=SAI3_SCK_A
PD1.Signal=SAI3_SD_A
PD10.Mode=RGB565
PD10.Signal=LTDC_B3
PD11.Mode=Single Bank 1
PD11.Signal=QUADSPI_BK1_IO0
PD12.Mode=Single Bank 1
PD12.Signal=QUADSPI_BK1_IO1
PD13.Mode=Single Bank 1
PD13.Signal=QUADSPI_BK1_IO3
PD3.Mode=RGB565
PD3.Signal=LTDC_G7
PD4.Signal=SAI3_FS_A
PE0.GPIOParameters=GPIO_Label
PE0.GPIO_Label=LED1
PE0.Signal=GPIO_Output
PE1.GPIOParameters=GPIO_Label
PE1.GPIO_Label=LED2
PE1.Signal=GPIO_Output
PE11.Mode=RGB565
PE11.Signal=LTDC_G3
PE12.Mode=RGB565
PE12.Signal=LTDC_B4
PE13.Mode=RGB565
PE13.Signal=LTDC_DE
PE14.Mode=RGB565
PE14.Signal=LTDC_CLK
PE15.Mode=RGB565
PE15.Signal=LTDC_R7
PE2.Mode=Single Bank 1
PE2.Signal=QUADSPI_BK1_IO2
PE3.GPIOParameters=GPIO_Label
PE3.GPIO_Label=LED3
PE3.Signal=GPIO_Output
PE4.GPIOParameters=PinState,GPIO_PuPd,GPIO_Label
PE4.GPIO_Label=TP_RST
PE4.GPIO_PuPd=GPIO_PULLUP
PE4.PinState=GPIO_PIN_SET
PE4.Signal=GPIO_Output
PE5.GPIOParameters=GPIO_PuPd,GPIO_Label
PE5.GPIO_Label=TP_INT
PE5.GPIO_PuPd=GPIO_PULLUP
PE5.Signal=GPIO_Input
PH0-OSC_IN\ (PH0).Mode=HSE-External-Oscillator
PH0-OSC_IN\ (PH0).Signal=RCC_OSC_IN
PH1-OSC_OUT\ (PH1).Mode=HSE-External-Oscillator
PH1-OSC_OUT\ (PH1).Signal=RCC_OSC_OUT
RCC.HSE_VALUE=20000000
RCC.SYSCLKFreq_VALUE=480000000
RCC.SYSCLKSource=RCC_SYSCLKSOURCE_PLLCLK
board=custom

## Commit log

2025-05-25 Update first version of schematic
2025-05-26 Pre position of components
2025-06-02 Placement
2025-06-12 att.
2025-06-13 Fix componentes possiton
2025-08-25 fix fpc
2025-09-02 fix lcd
2025-10-08 external loader
2025-10-10 initial
2025-10-19 works example
2025-10-21 fix touch
2025-10-28 added jpeg codec
2025-10-30 example run
